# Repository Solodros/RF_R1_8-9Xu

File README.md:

# RF_R1_8-9Xu

Open source universal PCB for the Realforce R1 family of keyboards.

## Introduction

This project is a continuation of my development of open source EC boards.

The supported layouts are the one of the Realforce R1 family of keyboards, it being ANSI, ISO or JIS.

## Technical information

- Layout size: tenkeykess (TKL)
- Compatible switches: EC switches (Topre and NIZ)
- Microcontroller: STM32F401
- Connector:
    * internal USB-C
    * original JST connector S4B-EH(LF)(SN)
    * jst connector for daughterboard
- Addressable RGB strip support
- Firmware compatibility: QMK (with VIA/VIAL support)
- Protection hardware (on all connection methods):
  * Fused
  * ESD protection

## Renders and Prototypes

### Render

### Prototype

## Revisions and relative features

### Rev1

This revision implements all the main features of the PCB.

#### Connectivity

Since this is first and foremost a replacement PCB for the original Realforce R1 PCB, the original JST connector is still supported. It's been moved to the right to accommodate the new JST connector for the daughterboard and the USB-C connector.

I thought about adding extra connectors so that if anyone wants to use this PCB in a custom project they can have the flexibility to use the connector that they prefer.

#### Addressable RGB strip support

Since the R1 PCB is used in some already existing custom PC (polycarbonate) cases, it was important to have a way to include a RGB strip support.

The strip can be directly sticked to the PCB and then wired to the PCB by soldering the pins to the THT pins or SMD pads.

Lighting can be controlled by the board itself and customization is achieved by using Vial/VIA.

### Rev 1.1

This revision implements the following changes:
  * added support for THT LED for Caps Lock and Scroll Lock
  * moved filtering components for plate shield to top side
  * added filtering components for USB-C shield
  * improved ground stitching

## "Why no plates?" I hear you say

It is what it is.

For real though, the PCB is a replacement for the original Realforce R1 PCB so using the original plates is the preferred option. Furthermore, the multilayout support makes it tedious to make a plate design for each and every layout.

Nevertheless, if there's a particular plate config you want to use, you can always open an issue on the repository or even better make a PR from your own fork.

## Copyright notice

This project is released under the MIT License. For the license, please refer to the LICENSE.md file.

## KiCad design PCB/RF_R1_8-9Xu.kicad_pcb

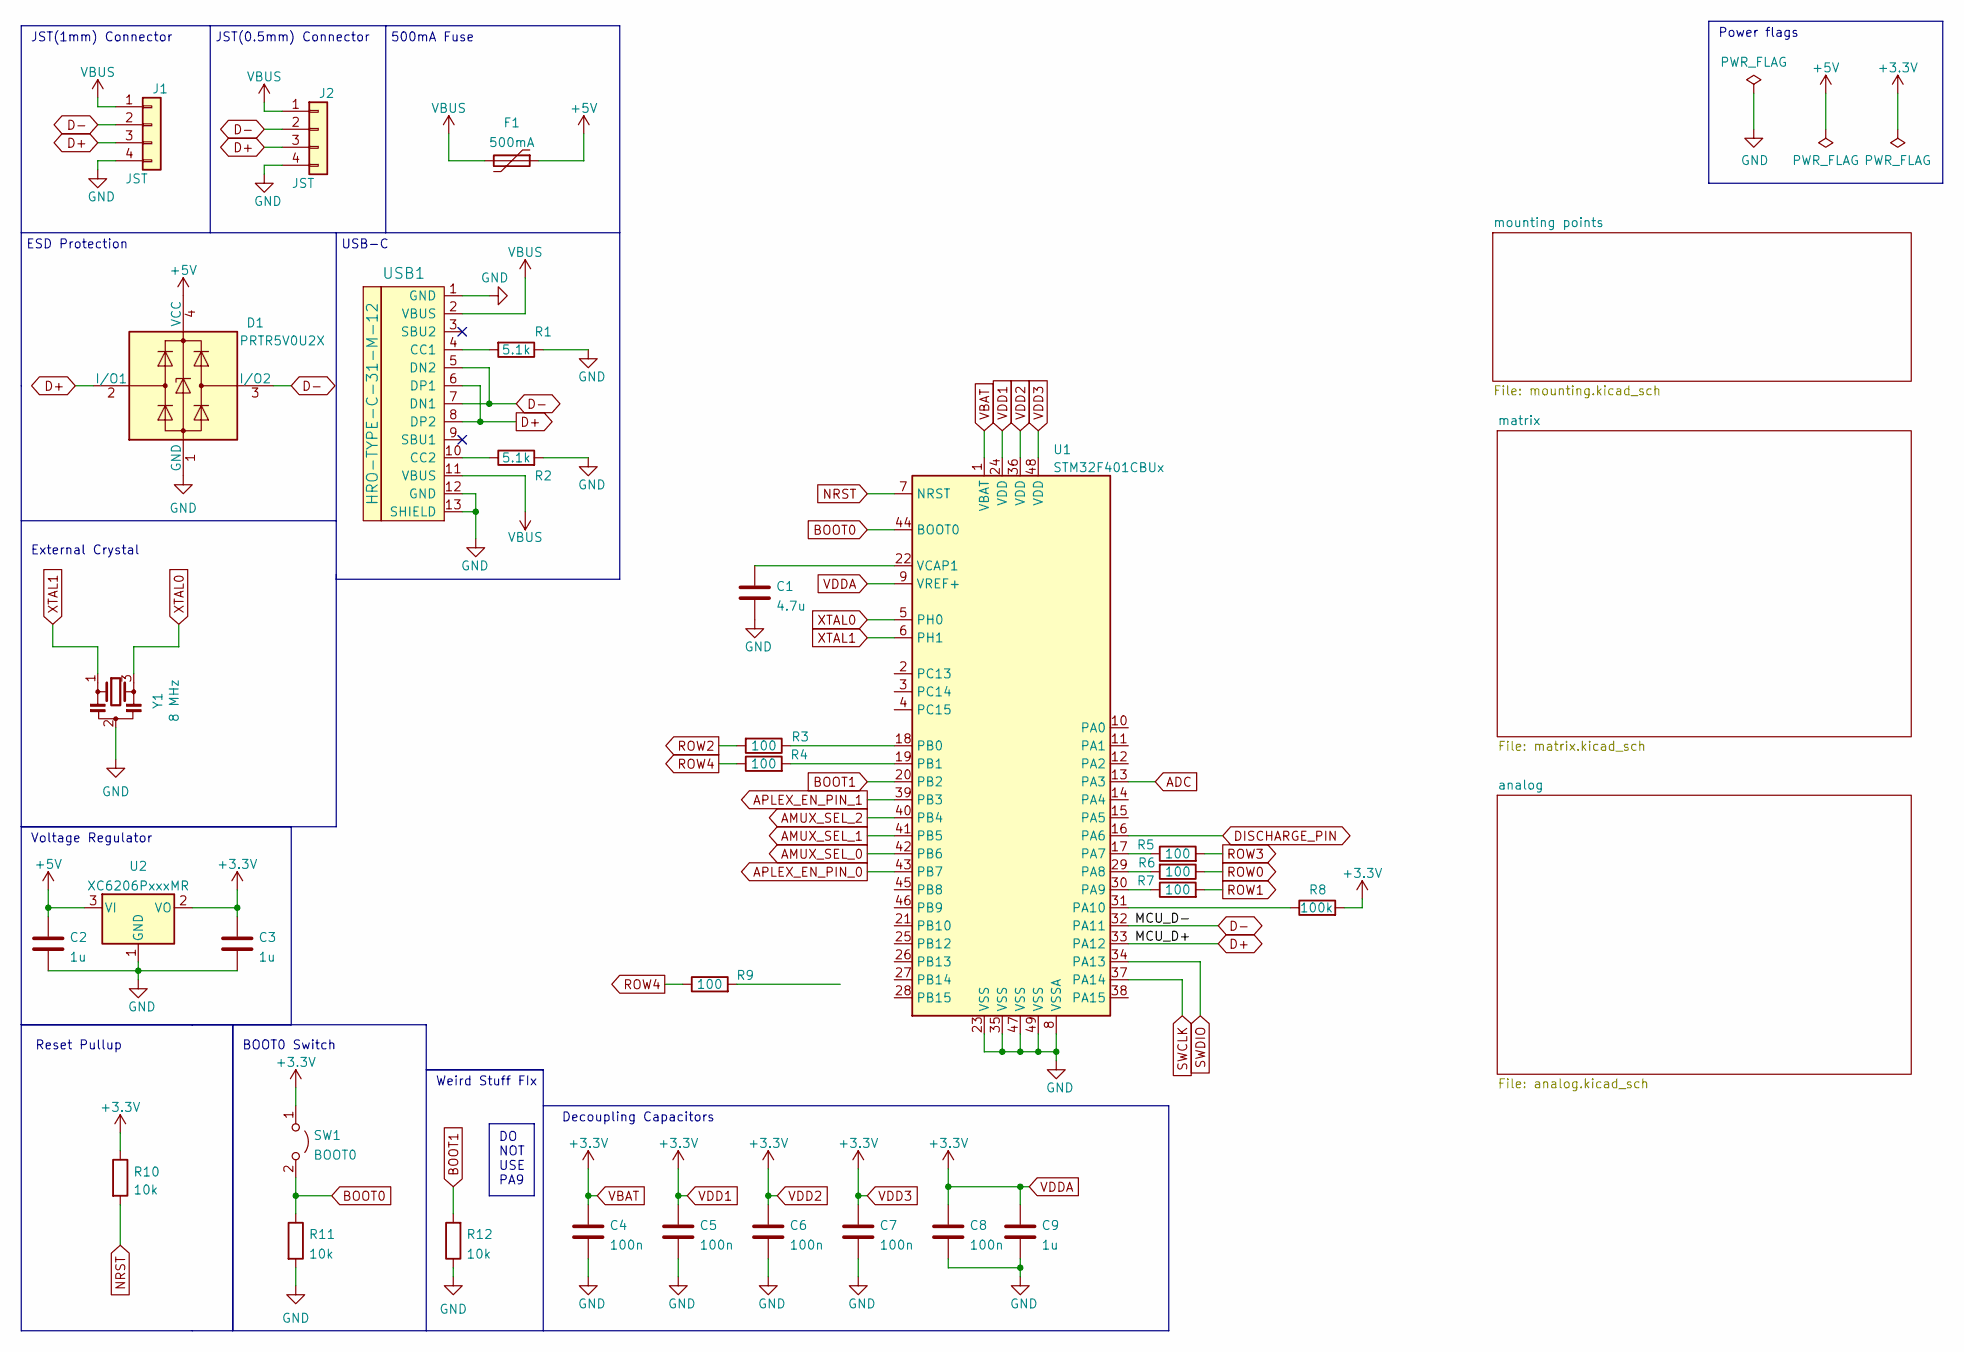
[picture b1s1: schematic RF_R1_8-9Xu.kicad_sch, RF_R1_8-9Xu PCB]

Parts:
C1: 4.7u; C_0402_1005Metric
C2, C3, C9: 1u; C_0402_1005Metric
C4, C5, C6, C7, C8: 100n; C_0402_1005Metric
D1: PRTR5V0U2X; SOT-143
F1: 500mA; Fuse_1206_3216Metric
J1: JST; JST_EH_S4B-EH_1x04_P2.50mm_Horizontal
J2: JST; JST-SR-4
R1, R2: 5.1k; R_0402_1005Metric
R3, R4, R5, R6, R7, R9: 100; R_0402_1005Metric
R8: 100k; R_0402_1005Metric
R10, R11, R12: 10k; R_0402_1005Metric
SW1: BOOT0; PinHeader_1x02_P2.54mm_Vertical
U1: STM32F401CBUx; QFN-48-1EP_7x7mm_P0.5mm_EP5.6x5.6mm
U2: XC6206PxxxMR; SOT-23
USB1: HRO-TYPE-C-31-M-12; HRO-TYPE-C-31-M-12-Assembly
Y1: 8 MHz; Resonator_SMD_Murata_CSTxExxV-3Pin_3.0x1.1mm; LCSC C907975

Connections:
+5V: C2.1, D1.4 (VCC), F1.1, U2.3 (VI)
ADC: U1.13 (PA3); also elsewhere on the board
AMUX_SEL_0: U1.42 (PB6); also elsewhere on the board
AMUX_SEL_1: U1.41 (PB5); also elsewhere on the board
AMUX_SEL_2: U1.40 (PB4); also elsewhere on the board
APLEX_EN_PIN_0: U1.43 (PB7); also elsewhere on the board
APLEX_EN_PIN_1: U1.39 (PB3); also elsewhere on the board
APLEX_OUT_PIN_0: U1.16 (PA6); also elsewhere on the board
BOOT0: R11.1, SW1.2 (B), U1.44 (BOOT0)
BOOT1: R12.2, U1.20 (PB2)
D+: D1.2 (I/O1), J1.3, J2.3, U1.33 (PA12), USB1.6 (DP1), USB1.8 (DP2)
D-: D1.3 (I/O2), J1.2, J2.2, U1.32 (PA11), USB1.5 (DN2), USB1.7 (DN1)
GND: C1.2, C2.2, C3.2, C4.2, C5.2, C6.2, C7.2, C8.2, C9.2, D1.1 (GND), J1.4, J2.4, R1.1, R2.2, R11.2, R12.1, U1.8 (VSSA), U1.23 (VSS), U1.35 (VSS), U1.47 (VSS), U1.49 (VSS), U2.1 (GND), USB1.1 (GND), USB1.12 (GND), USB1.13 (SHIELD), Y1.2; also elsewhere on the board
NRST: R10.2, U1.7 (NRST)
unnamed: C1.1, U1.22 (VCAP1)
unnamed: R1.2, USB1.4 (CC1)
unnamed: R2.1, USB1.10 (CC2)
unnamed: R3.1, U1.18 (PB0)
unnamed: R4.2, U1.19 (PB1)
unnamed: R5.1, U1.17 (PA7)
unnamed: R6.2, U1.29 (PA8)
unnamed: R7.1, U1.30 (PA9)
unnamed: R8.1, U1.31 (PA10)
ROW0: R6.1; also elsewhere on the board
ROW1: R7.2; also elsewhere on the board
ROW2: R3.2; also elsewhere on the board
ROW3: R5.2; also elsewhere on the board
ROW4: R4.1, R9.1; also elsewhere on the board
SWCLK: U1.37 (PA14)
SWDIO: U1.34 (PA13)
VBAT: C3.1, C4.1, C5.1, C6.1, C7.1, C8.1, C9.1, R8.2, R10.1, SW1.1 (A), U1.1 (VBAT), U1.9 (VREF+), U1.24 (VDD), U1.36 (VDD), U1.48 (VDD), U2.2 (VO); also elsewhere on the board
VBUS: F1.2, J1.1, J2.1, USB1.2 (VBUS), USB1.11 (VBUS)
XTAL0: U1.5 (PH0), Y1.3
XTAL1: U1.6 (PH1), Y1.1

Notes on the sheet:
DO NOT USE PA9
USB-C
Voltage Regulator
JST(1mm) Connector
JST(0.5mm) Connector
BOOT0 Switch
External Crystal
500mA Fuse
Weird Stuff FIx
Decoupling Capacitors
Power flags
ESD Protection
Reset Pullup

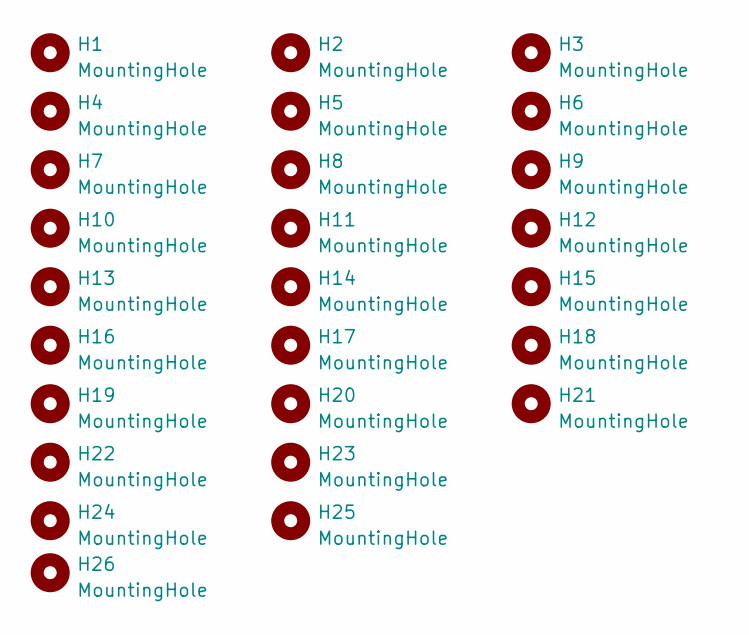
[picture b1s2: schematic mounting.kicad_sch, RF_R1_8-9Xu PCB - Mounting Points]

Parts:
H1, H2, H3, H4, H5, H6, H7, H8, H9, H10, H11, H12, H13, H14, H15, H16, H17, H18, H19, H20, H21, H22, H23, H24, H25, H26: MountingHole; HOLE_M2_RF

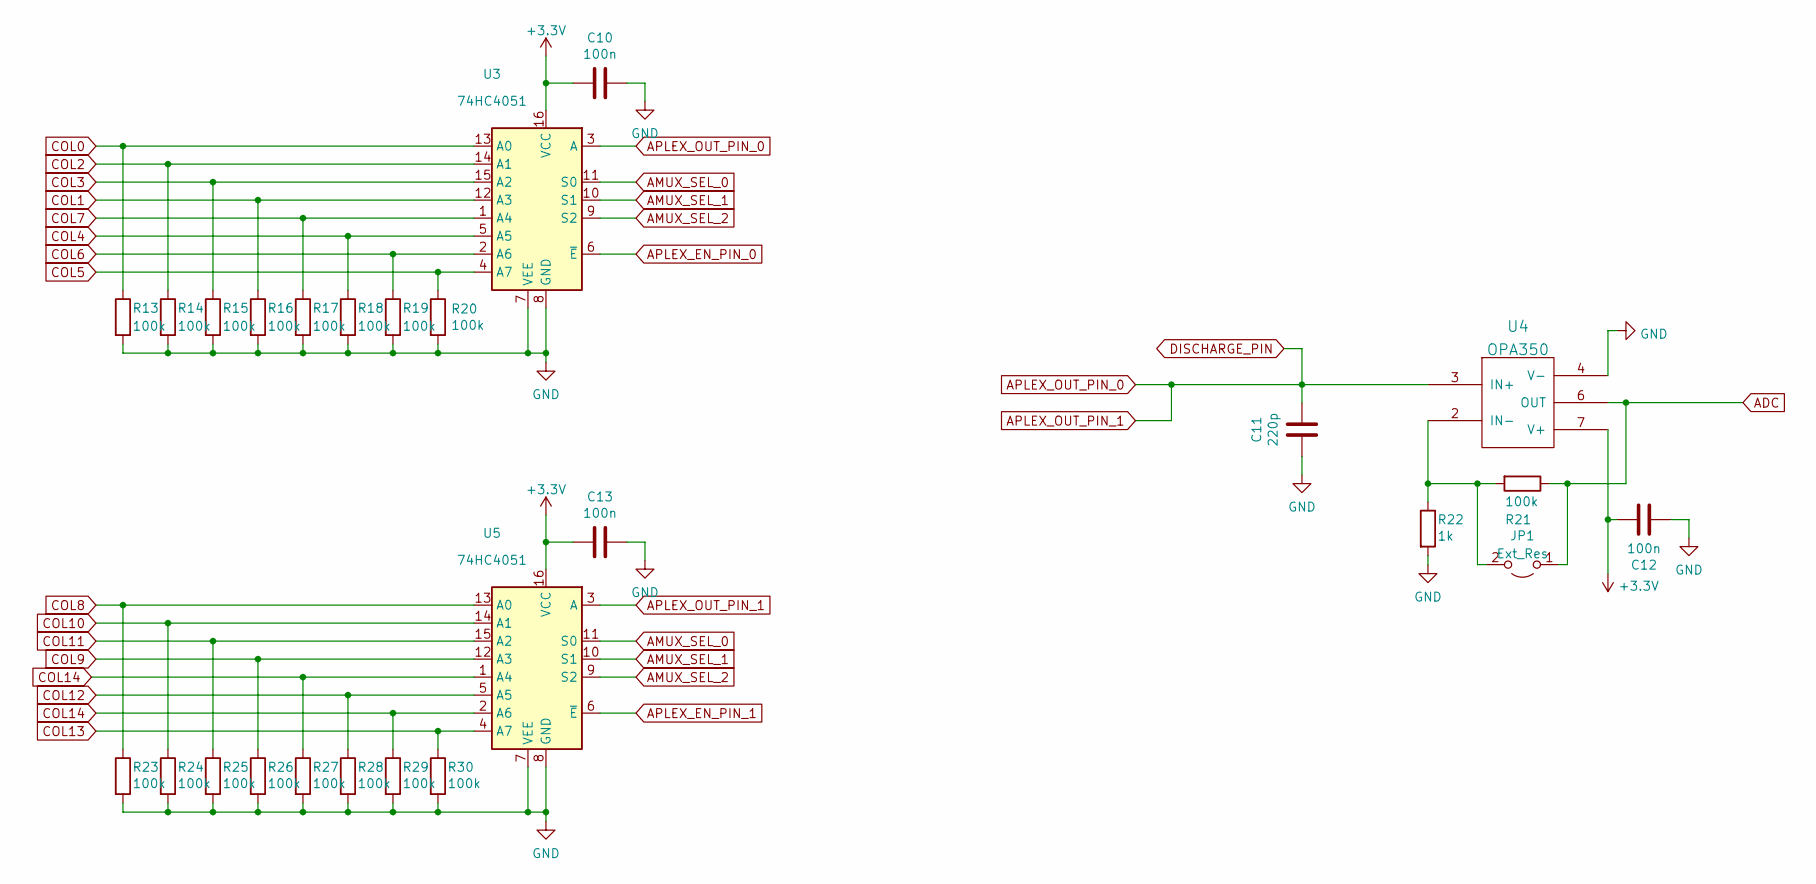
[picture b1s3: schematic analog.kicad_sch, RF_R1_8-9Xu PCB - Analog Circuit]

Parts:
C10, C12, C13: 100n; C_0402_1005Metric
C11: 220p; C_0402_1005Metric
JP1: Ext_Res; R_0603_1608Metric_Pad0.98x0.95mm_HandSolder
R13, R14, R15, R16, R17, R18, R19, R20, R21, R23, R24, R25, R26, R27, R28, R29, R30: 100k; R_0402_1005Metric
R22: 1k; R_0402_1005Metric
U3, U5: 74HC4051; TSSOP16
U4: OPA350; SOIC-8_3.9x4.9mm_P1.27mm

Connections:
ADC: JP1.1 (A), R21.1, U4.6 (OUT); also elsewhere on the board
AMUX_SEL_0: U3.11 (S0), U5.11 (S0); also elsewhere on the board
AMUX_SEL_1: U3.10 (S1), U5.10 (S1); also elsewhere on the board
AMUX_SEL_2: U3.9 (S2), U5.9 (S2); also elsewhere on the board
APLEX_EN_PIN_0: U3.6 (~E); also elsewhere on the board
APLEX_EN_PIN_1: U5.6 (~E); also elsewhere on the board
APLEX_OUT_PIN_0: C11.1, U3.3 (A), U4.3 (IN+), U5.3 (A); also elsewhere on the board
COL0: R13.1, U3.13 (A0); also elsewhere on the board
COL1: R16.1, U3.12 (A3); also elsewhere on the board
COL2: R14.1, U3.14 (A1); also elsewhere on the board
COL3: R15.1, U3.15 (A2); also elsewhere on the board
COL4: R18.1, U3.5 (A5); also elsewhere on the board
COL5: R20.1, U3.4 (A7); also elsewhere on the board
COL6: R19.1, U3.2 (A6); also elsewhere on the board
COL7: R17.1, U3.1 (A4); also elsewhere on the board
COL8: R23.1, U5.13 (A0); also elsewhere on the board
COL9: R26.1, U5.12 (A3); also elsewhere on the board
COL10: R24.1, U5.14 (A1); also elsewhere on the board
COL11: R25.1, U5.15 (A2); also elsewhere on the board
COL12: R28.1, U5.5 (A5); also elsewhere on the board
COL13: R30.1, U5.4 (A7); also elsewhere on the board
COL14: R27.1, R29.1, U5.1 (A4), U5.2 (A6); also elsewhere on the board
GND: C10.1, C11.2, C12.1, C13.1, R13.2, R14.2, R15.2, R16.2, R17.2, R18.2, R19.2, R20.2, R22.2, R23.2, R24.2, R25.2, R26.2, R27.2, R28.2, R29.2, R30.2, U3.7 (VEE), U3.8 (GND), U4.4 (V-), U5.7 (VEE), U5.8 (GND); also elsewhere on the board
unnamed: JP1.2 (B), R21.2, R22.1, U4.2 (IN-)
VBAT: C10.2, C12.2, C13.2, U3.16 (VCC), U4.7 (V+), U5.16 (VCC); also elsewhere on the board

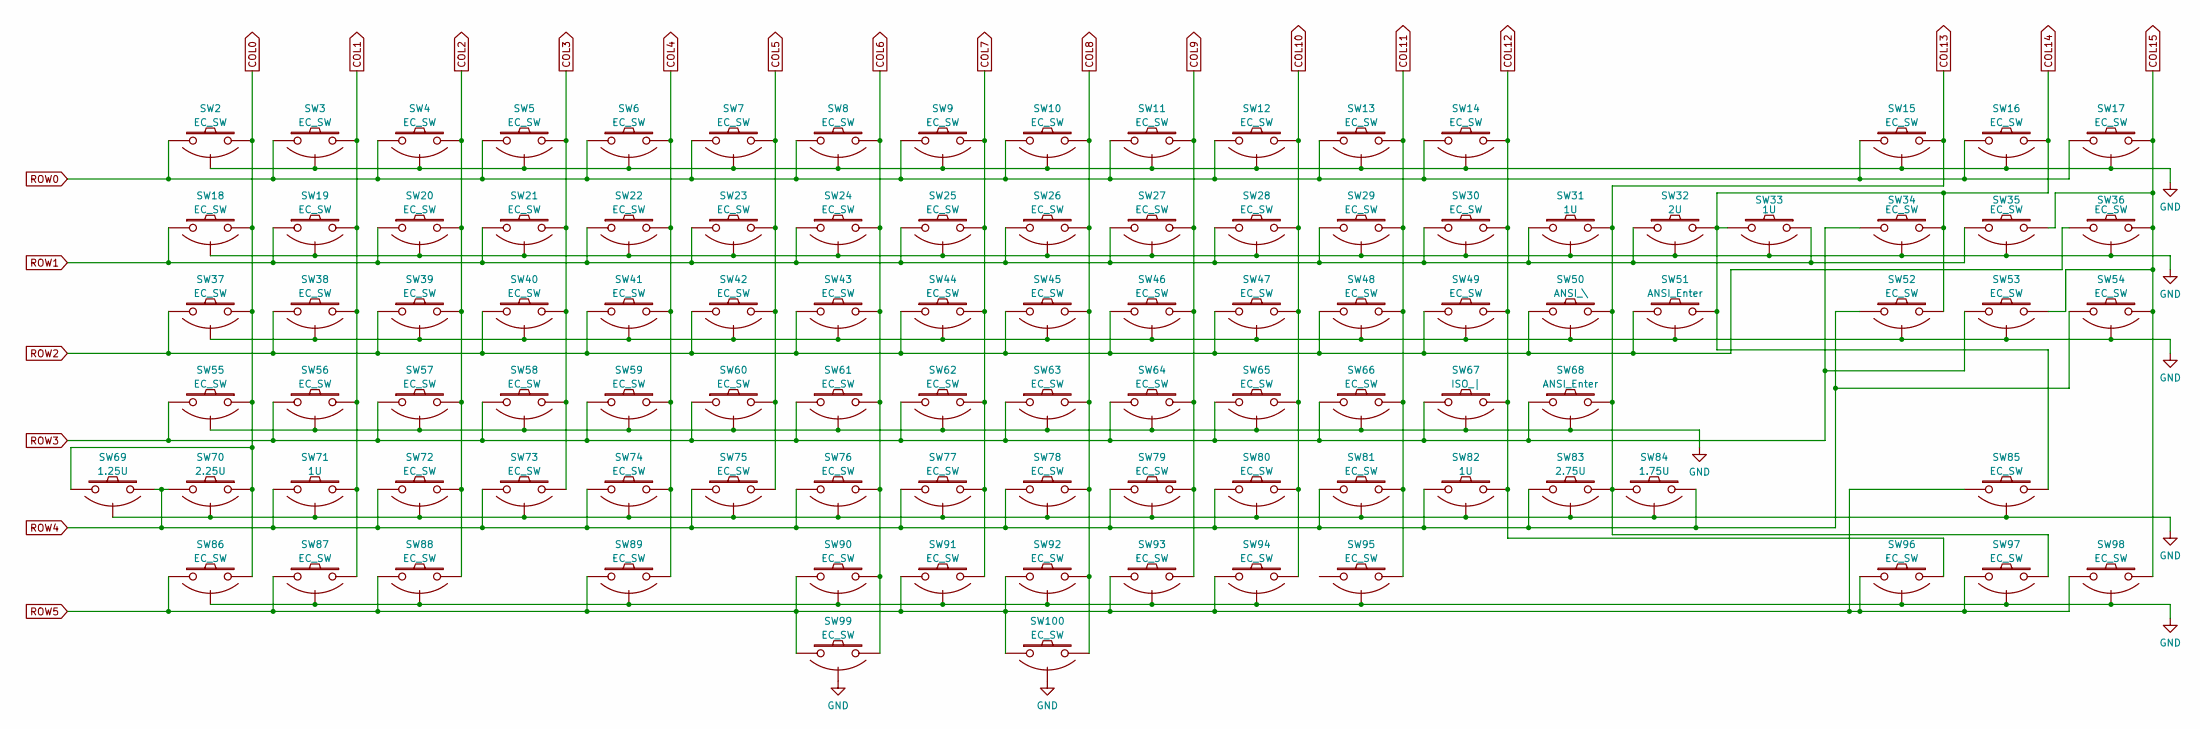
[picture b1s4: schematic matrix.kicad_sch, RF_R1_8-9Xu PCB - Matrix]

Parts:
SW2, SW3, SW4, SW5, SW6, SW7, SW8, SW9, SW10, SW11, SW12, SW13, SW14, SW15, SW16, SW17, SW18, SW19, SW20, SW21, SW22, SW23, SW24, SW25, SW26, SW27, SW28, SW29, SW30, SW34, SW35, SW36, SW37, SW38, SW39, SW40, SW41, SW42, SW43, SW44, SW45, SW46, SW47, SW48, SW49, SW52, SW53, SW54, SW56, SW57, SW58, SW59, SW60, SW61, SW62, SW63, SW64, SW65, SW66, SW72, SW73, SW74, SW75, SW76, SW77, SW78, SW79, SW80, SW81, SW85, SW86, SW87, SW88, SW89, SW91, SW92, SW94, SW95, SW96, SW97, SW98, SW99, SW100: EC_SW; ecs_pad_no_ring
SW31, SW33, SW82: 1U; ecs_pad_no_ring
SW32: 2U; ecs_pad_no_ring
SW50: ANSI_\; ecs_pad_no_ring
SW51, SW68: ANSI_Enter; ecs_pad_no_ring
SW55, SW90, SW93: EC_SW; ecs_pad_no_ring_stepped&normal
SW67: ISO_|; ecs_pad_no_ring
SW69: 1.25U; ecs_pad_no_ring
SW70: 2.25U; ecs_pad_no_ring_1u_edge_cut
SW71: 1U; ecs_pad_no_ring_1u_edge_cut
SW83: 2.75U; ecs_pad_no_ring
SW84: 1.75U; ecs_pad_no_ring

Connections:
COL0: SW2.2, SW18.2, SW37.2, SW55.1, SW69.2, SW70.1, SW86.2; also elsewhere on the board
COL1: SW3.2, SW19.2, SW38.2, SW56.2, SW71.2, SW87.2; also elsewhere on the board
COL2: SW4.2, SW20.2, SW39.2, SW57.2, SW72.2, SW88.2; also elsewhere on the board
COL3: SW5.2, SW21.2, SW40.2, SW58.2, SW73.2; also elsewhere on the board
COL4: SW6.2, SW22.2, SW41.2, SW59.2, SW74.2, SW89.2; also elsewhere on the board
COL5: SW7.2, SW23.2, SW42.2, SW60.2, SW75.2; also elsewhere on the board
COL6: SW8.2, SW24.2, SW43.2, SW61.2, SW76.2, SW90.2, SW99.2; also elsewhere on the board
COL7: SW9.2, SW25.2, SW44.2, SW62.2, SW77.2, SW91.2; also elsewhere on the board
COL8: SW10.2, SW26.2, SW45.2, SW63.2, SW78.2, SW92.2, SW100.2; also elsewhere on the board
COL9: SW11.2, SW27.2, SW46.2, SW64.2, SW79.2, SW93.2; also elsewhere on the board
COL10: SW12.2, SW28.2, SW47.2, SW65.2, SW80.2, SW94.2; also elsewhere on the board
COL11: SW13.2, SW29.2, SW48.2, SW66.2, SW81.2, SW95.2; also elsewhere on the board
COL12: SW14.2, SW30.2, SW49.2, SW67.2, SW82.2, SW96.2; also elsewhere on the board
COL13: SW15.2, SW31.2, SW50.2, SW68.2, SW83.2, SW84.2, SW97.2; also elsewhere on the board
COL14: SW16.2, SW32.2, SW33.2, SW34.2, SW51.2, SW52.2, SW85.2; also elsewhere on the board
COL15: SW17.2, SW35.2, SW36.2, SW53.2, SW54.2, SW98.2
GND: SW2.3 (SG), SW3.3 (SG), SW4.3 (SG), SW5.3 (SG), SW6.3 (SG), SW7.3 (SG), SW8.3 (SG), SW9.3 (SG), SW10.3 (SG), SW11.3 (SG), SW12.3 (SG), SW13.3 (SG), SW14.3 (SG), SW15.3 (SG), SW16.3 (SG), SW17.3 (SG), SW18.3 (SG), SW19.3 (SG), SW20.3 (SG), SW21.3 (SG), SW22.3 (SG), SW23.3 (SG), SW24.3 (SG), SW25.3 (SG), SW26.3 (SG), SW27.3 (SG), SW28.3 (SG), SW29.3 (SG), SW30.3 (SG), SW31.3 (SG), SW32.3 (SG), SW33.3 (SG), SW34.3 (SG), SW35.3 (SG), SW36.3 (SG), SW37.3 (SG), SW38.3 (SG), SW39.3 (SG), SW40.3 (SG), SW41.3 (SG), SW42.3 (SG), SW43.3 (SG), SW44.3 (SG), SW45.3 (SG), SW46.3 (SG), SW47.3 (SG), SW48.3 (SG), SW49.3 (SG), SW50.3 (SG), SW51.3 (SG), SW52.3 (SG), SW53.3 (SG), SW54.3 (SG), SW55.3 (SG), SW56.3 (SG), SW57.3 (SG), SW58.3 (SG), SW59.3 (SG), SW60.3 (SG), SW61.3 (SG), SW62.3 (SG), SW63.3 (SG), SW64.3 (SG), SW65.3 (SG), SW66.3 (SG), SW67.3 (SG), SW68.3 (SG), SW69.3 (SG), SW70.3 (SG), SW71.3 (SG), SW72.3 (SG), SW73.3 (SG), SW74.3 (SG), SW75.3 (SG), SW76.3 (SG), SW77.3 (SG), SW78.3 (SG), SW79.3 (SG), SW80.3 (SG), SW81.3 (SG), SW82.3 (SG), SW83.3 (SG), SW84.3 (SG), SW85.3 (SG), SW86.3 (SG), SW87.3 (SG), SW88.3 (SG), SW89.3 (SG), SW90.3 (SG), SW91.3 (SG), SW92.3 (SG), SW93.3 (SG), SW94.3 (SG), SW95.3 (SG), SW96.3 (SG), SW97.3 (SG), SW98.3 (SG), SW99.3 (SG), SW100.3 (SG); also elsewhere on the board
ROW0: SW2.1, SW3.1, SW4.1, SW5.1, SW6.1, SW7.1, SW8.1, SW9.1, SW10.1, SW11.1, SW12.1, SW13.1, SW14.1, SW15.1, SW16.1, SW17.1; also elsewhere on the board
ROW1: SW18.1, SW19.1, SW20.1, SW21.1, SW22.1, SW23.1, SW24.1, SW25.1, SW26.1, SW27.1, SW28.1, SW29.1, SW30.1, SW31.1, SW32.1, SW33.1, SW35.1; also elsewhere on the board
ROW2: SW36.1, SW37.1, SW38.1, SW39.1, SW40.1, SW41.1, SW42.1, SW43.1, SW44.1, SW45.1, SW46.1, SW47.1, SW48.1, SW49.1, SW50.1, SW51.1; also elsewhere on the board
ROW3: SW34.1, SW53.1, SW55.2, SW56.1, SW57.1, SW58.1, SW59.1, SW60.1, SW61.1, SW62.1, SW63.1, SW64.1, SW65.1, SW66.1, SW67.1, SW68.1; also elsewhere on the board
ROW4: SW52.1, SW54.1, SW69.1, SW70.2, SW71.1, SW72.1, SW73.1, SW74.1, SW75.1, SW76.1, SW77.1, SW78.1, SW79.1, SW80.1, SW81.1, SW82.1, SW83.1, SW84.1; also elsewhere on the board
ROW5: SW85.1, SW86.1, SW87.1, SW88.1, SW89.1, SW90.1, SW91.1, SW92.1, SW93.1, SW94.1, SW96.1, SW97.1, SW98.1, SW99.1, SW100.1

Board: 4 copper layers, 181 parts (0 on the bottom side), 50 nets, no tracks yet.

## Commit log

2022-08-02 Init
2022-08-09 Update and pre-production output
2022-08-09 Update for new part
2022-08-09 Schematic update
2022-08-10 Final PCB Rev
2022-08-10 Typos fix
2022-08-10 Fix PA9 being used
2022-08-12 Production files update
2022-08-22 Firmware upload after testing
2022-08-23 Proto pic upload
2022-08-27 Render pictures update
2022-08-27 Update of PCB
    Added shielding copper pad for plate electrical connection, along with EMI filtering through capacitor and inductor.
2022-08-27 Update README.md
    fix typo
2022-08-28 Changed deactivation point to higher reading
2022-09-26 Firmware Update
    Firmware update to allow for single layout option customization instead of presets.
2022-10-01 Enabled mouse in rules
2022-10-17 Update of threshold values and handling.
2022-12-03 Delete via.json
    removed bc used in previous revision
2022-12-13 Updated files for Rev 1.1
    Features added:
    - THT LED for Caps Lock and Scroll Lock
    - moved filtering components for plate shield to top side
    - added filtering components for USB-C shield
    Firmware updated accordingly too.
2023-01-01 Fix in label text
2023-01-09 Updated footprints and relative models
2023-01-15 Refactoring of codebase.
2023-03-20 VIA Update
    VIA Firmware update
2023-08-16 Addition of new FW
    New Sideload firmware release that enables new features as:
    - Rapid Trigger (still WIP with bugs)
    - Calibration
    Compatible with previous revisions PCBs.
2023-08-18 AMUX init function consolidation
